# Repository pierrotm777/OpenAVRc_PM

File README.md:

# OpenAVRc_PM
 My own OpenAVRc DEV for test only

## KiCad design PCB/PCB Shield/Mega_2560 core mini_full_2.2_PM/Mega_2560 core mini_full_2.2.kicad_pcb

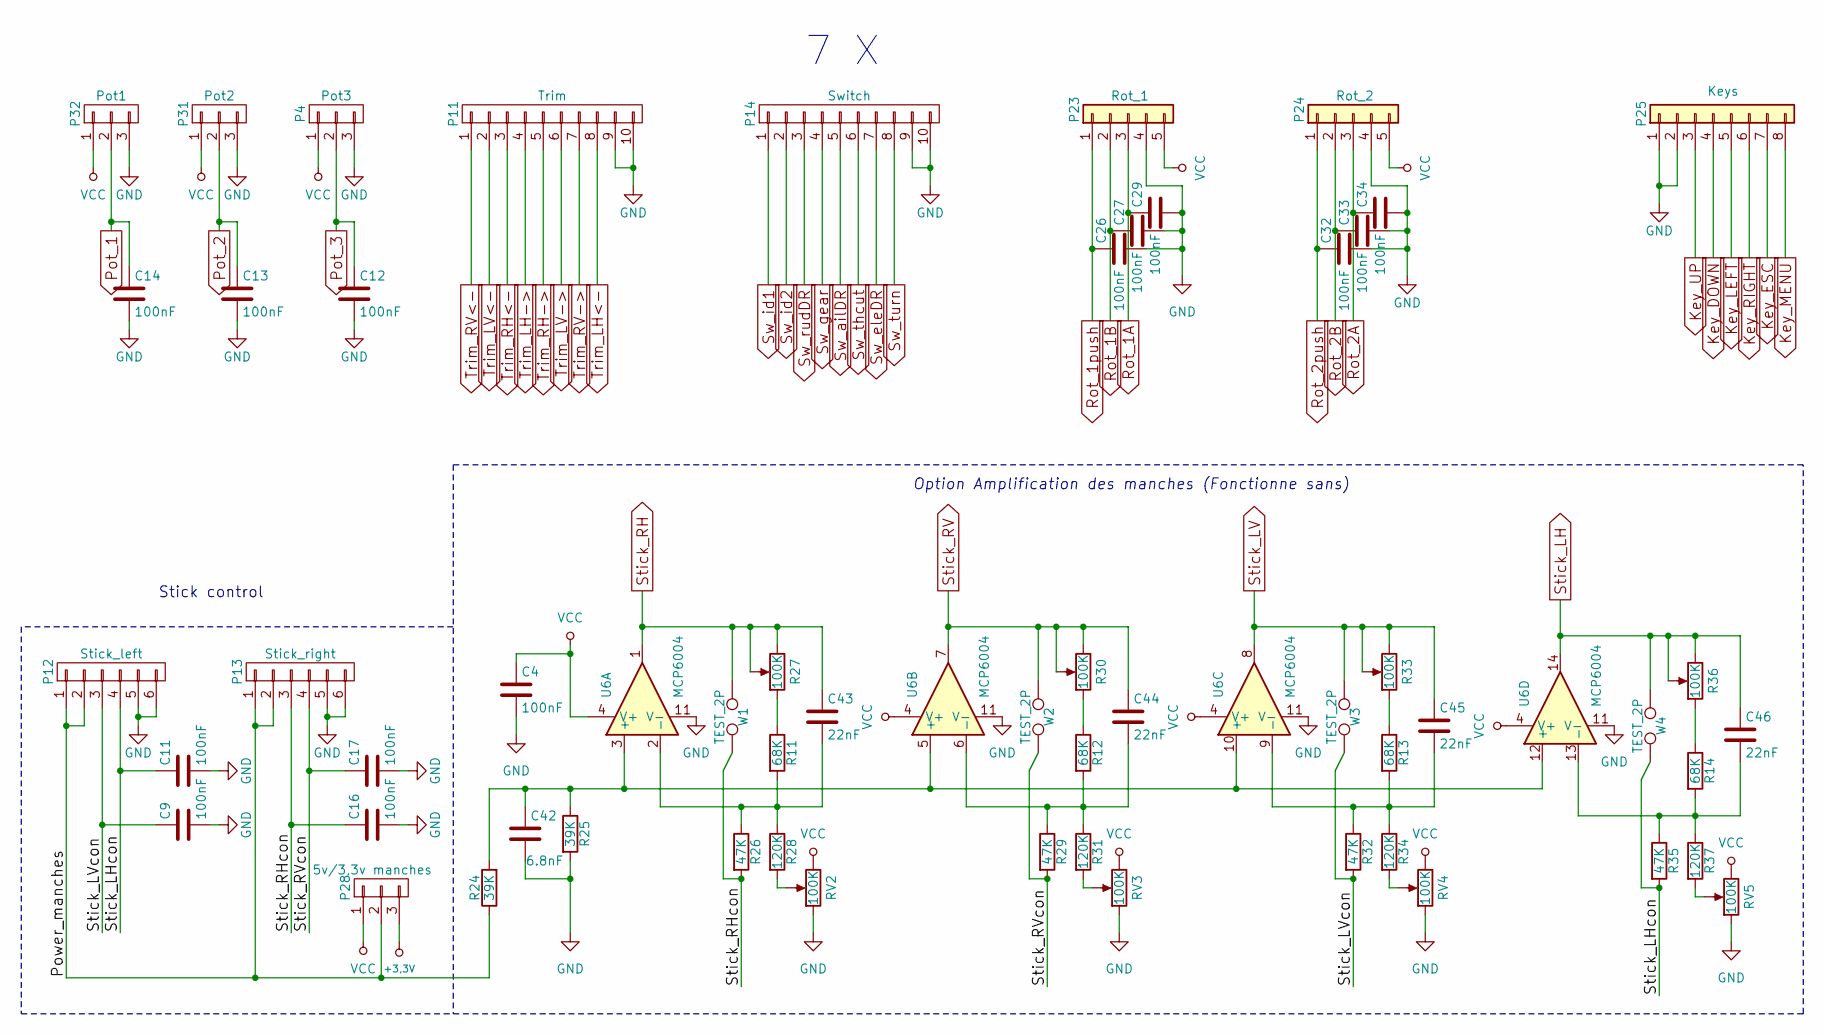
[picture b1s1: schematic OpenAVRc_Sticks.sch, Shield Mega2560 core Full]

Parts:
C4, C9, C11, C12, C13, C14, C16, C17, C26, C27, C29, C32, C33, C34: 100nF; C_1206
C42: 6.8nF; C_1206
C43, C44, C45, C46: 22nF; C_1206
P4: Pot3; Pin_Header_Straight_1x03_Pitch2.54mm
P11: Trim; Pin_Header_Straight_2x05_Pitch2.54mm
P12: Stick_left; Pin_Header_Straight_2x03_Pitch2.54mm
P13: Stick_right; Pin_Header_Straight_2x03_Pitch2.54mm
P14: Switch; Pin_Header_Straight_2x05_Pitch2.54mm
P23: Rot_1; Pin_Header_Straight_1x05_Pitch2.54mm
P24: Rot_2; Pin_Header_Straight_1x05_Pitch2.54mm
P25: Keys; Pin_Header_Straight_2x04_Pitch2.54mm
P28: 5v/3,3v manches; Pin_Header_Straight_1x03_Pitch2.54mm
P31: Pot2; Pin_Header_Straight_1x03_Pitch2.54mm
P32: Pot1; Pin_Header_Straight_1x03_Pitch2.54mm
R11, R12, R13, R14: 68K; R_1206
R24, R25: 39K; R_1206
R26, R29, R32, R35: 47K; R_1206
R27, R30, R33, R36: 100K; Potentiometer_Trimmer_Bourns_3296W
R28, R31, R34, R37: 120K; R_1206
RV2, RV3, RV4, RV5: 100K; Potentiometer_Bourns_3296W_3-8Zoll_Inline_ScrewUp
U6: MCP6004; SOP14
W1, W2, W3, W4: TEST_2P; TESTPT

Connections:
+3.3V: P28.3; also elsewhere on the board
/OpenAVRc_Sticks/Power_manches: P12.1, P12.2, P13.1, P13.2, P28.2, R24.1
/OpenAVRc_Sticks/Stick_LHcon: C11.1, P12.4, R35.2, W4.2
/OpenAVRc_Sticks/Stick_LVcon: C9.1, P12.3, R32.2, W3.2
/OpenAVRc_Sticks/Stick_RHcon: C16.1, P13.3, R26.2, W1.2
/OpenAVRc_Sticks/Stick_RVcon: C17.1, P13.4, R29.2, W2.2
GND: C4.2, C9.2, C11.2, C12.2, C13.2, C14.2, C16.2, C17.2, C26.2, C27.2, C29.2, C32.2, C33.2, C34.2, C42.2, P4.3, P11.9, P11.10, P12.5, P12.6, P13.5, P13.6, P14.9, P14.10, P23.4, P24.4, P25.1, P25.2, P31.3, P32.3, R25.2, RV2.1, RV3.1, RV4.1, RV5.1, U6.11 (V-); also elsewhere on the board
Key_DOWN: P25.4; also elsewhere on the board
Key_ESC: P25.7; also elsewhere on the board
Key_LEFT: P25.5; also elsewhere on the board
Key_MENU: P25.8; also elsewhere on the board
Key_RIGHT: P25.6; also elsewhere on the board
Key_UP: P25.3; also elsewhere on the board
unnamed: C42.1, R24.2, R25.1, U6.3 (+), U6.5 (+), U6.10 (+), U6.12 (+)
unnamed: C43.2, R11.2, R26.1, R28.1, U6.2 (-)
unnamed: C44.2, R12.2, R29.1, R31.1, U6.6 (-)
unnamed: C45.2, R13.2, R32.1, R34.1, U6.9 (-)
unnamed: C46.2, R14.2, R35.1, R37.1, U6.13 (-)
unnamed: R11.1, R27.1
unnamed: R12.1, R30.1
unnamed: R13.1, R33.1
unnamed: R14.1, R36.1
unnamed: R28.2, RV2.2
unnamed: R31.2, RV3.2
unnamed: R34.2, RV4.2
unnamed: R37.2, RV5.2
Pot_1: C14.1, P32.2; also elsewhere on the board
Pot_2: C13.1, P31.2; also elsewhere on the board
Pot_3: C12.1, P4.2; also elsewhere on the board
Rot_1A: C29.1, P23.3; also elsewhere on the board
Rot_1B: C27.1, P23.2; also elsewhere on the board
Rot_1push: C26.1, P23.1; also elsewhere on the board
Rot_2A: C34.1, P24.3; also elsewhere on the board
Rot_2B: C33.1, P24.2; also elsewhere on the board
Rot_2push: C32.1, P24.1; also elsewhere on the board
Stick_LH: C46.1, R36.2, R36.3, U6.14, W4.1; also elsewhere on the board
Stick_LV: C45.1, R33.2, R33.3, U6.8, W3.1; also elsewhere on the board
Stick_RH: C43.1, R27.2, R27.3, U6.1, W1.1; also elsewhere on the board
Stick_RV: C44.1, R30.2, R30.3, U6.7, W2.1; also elsewhere on the board
Sw_ailDR: P14.5; also elsewhere on the board
Sw_eleDR: P14.7; also elsewhere on the board
Sw_gear: P14.4; also elsewhere on the board
Sw_id1: P14.1; also elsewhere on the board
Sw_id2: P14.2; also elsewhere on the board
Sw_rudDR: P14.3; also elsewhere on the board
Sw_thcut: P14.6; also elsewhere on the board
Sw_turn: P14.8; also elsewhere on the board
Trim_LH->: P11.4; also elsewhere on the board
Trim_LH<-: P11.8; also elsewhere on the board
Trim_LV->: P11.6; also elsewhere on the board
Trim_LV<-: P11.2; also elsewhere on the board
Trim_RH->: P11.5; also elsewhere on the board
Trim_RH<-: P11.3; also elsewhere on the board
Trim_RV->: P11.7; also elsewhere on the board
Trim_RV<-: P11.1; also elsewhere on the board
VCC: C4.1, P4.1, P23.5, P24.5, P28.1, P31.1, P32.1, RV2.3, RV3.3, RV4.3, RV5.3, U6.4 (V+); also elsewhere on the board

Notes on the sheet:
Stick control
Option Amplification des manches (Fonctionne sans)
7 X

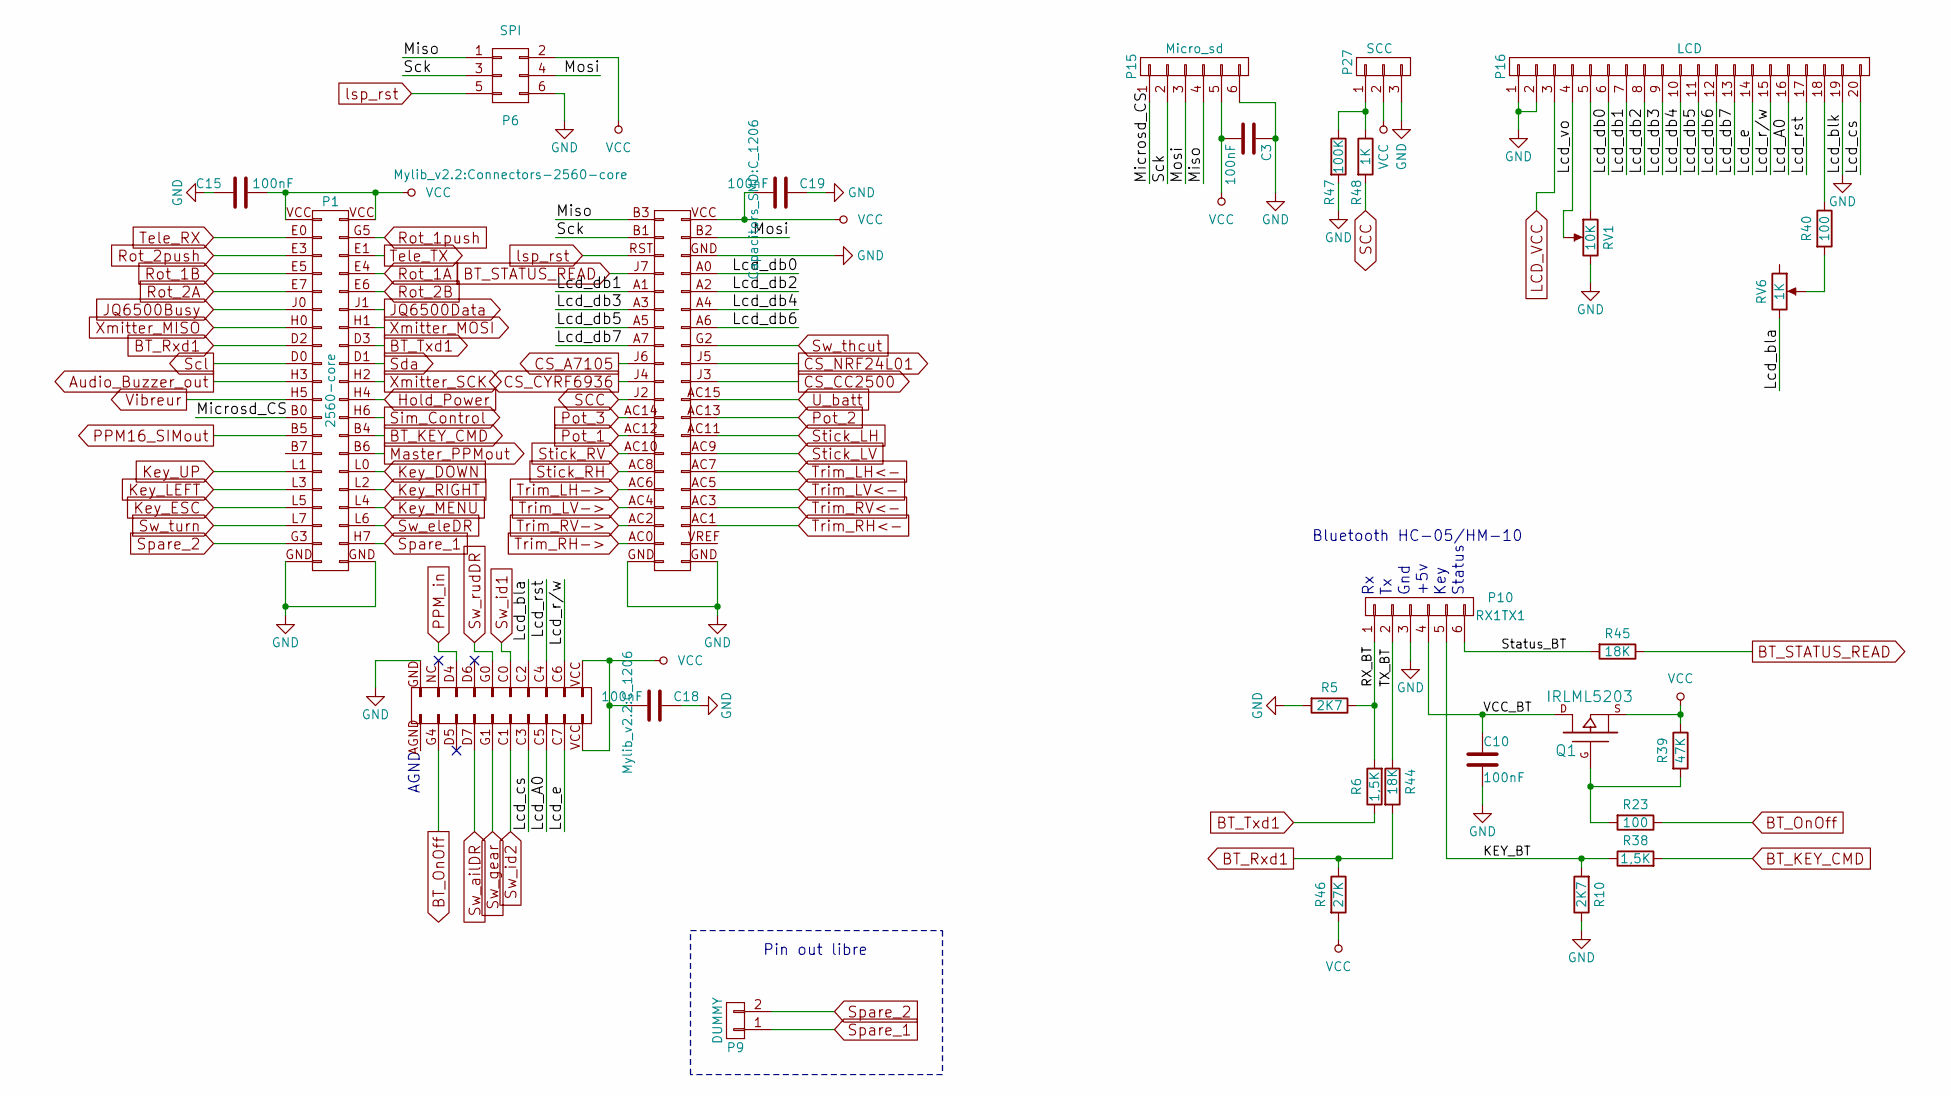
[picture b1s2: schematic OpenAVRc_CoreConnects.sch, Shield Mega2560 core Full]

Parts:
C3, C10, C15, C18, C19: 100nF; C_1206
P1: 2560-core; Connectors-2560-core
P6: SPI; Pin_Header_Straight_2x03_Pitch2.54mm
P9: DUMMY; Pin_Header_Straight_1x02_Pitch2.54mm
P10: RX1TX1; Pin_Header_Straight_1x06_Pitch2.54mm
P15: Micro_sd; Pin_Header_Straight_1x06_Pitch2.54mm
P16: LCD; Pin_Header_Straight_2x10_Pitch2.54mm
P27: SCC; Pin_Header_Straight_1x03_Pitch2.54mm
Q1: IRLML5203; SOT-23_MOS_P
R5, R10: 2K7; R_1206
R6, R38: 1,5K; R_1206
R23, R40: 100; R_1206
R39: 47K; R_1206
R44, R45: 18K; R_1206
R46: 27K; R_1206
R47: 100K; R_1206
R48: 1K; R_1206
RV1: 10K; Potentiometer_Trimmer_Bourns_3296W
RV6: 1K; Potentiometer_Trimmer_Bourns_3296W

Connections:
/OpenAVRc_CoreConnects/KEY_BT: P10.5, R10.2, R38.1
/OpenAVRc_CoreConnects/Lcd_A0: P1.C5 (P85), P16.16
/OpenAVRc_CoreConnects/Lcd_bla: P1.C2 (P88), RV6.3
/OpenAVRc_CoreConnects/Lcd_cs: P1.C3 (P87), P16.20
/OpenAVRc_CoreConnects/Lcd_db0: P1.A0 (P74), P16.6
/OpenAVRc_CoreConnects/Lcd_db1: P1.A1 (P71), P16.7
/OpenAVRc_CoreConnects/Lcd_db2: P1.A2 (P72), P16.8
/OpenAVRc_CoreConnects/Lcd_db3: P1.A3 (P69), P16.9
/OpenAVRc_CoreConnects/Lcd_db4: P1.A4 (P70), P16.10
/OpenAVRc_CoreConnects/Lcd_db5: P1.A5 (P67), P16.11
/OpenAVRc_CoreConnects/Lcd_db6: P1.A6 (P68), P16.12
/OpenAVRc_CoreConnects/Lcd_db7: P1.A7 (P65), P16.13
/OpenAVRc_CoreConnects/Lcd_e: P1.C7 (P83), P16.14
/OpenAVRc_CoreConnects/Lcd_r/w: P1.C6 (P84), P16.15
/OpenAVRc_CoreConnects/Lcd_rst: P1.C4 (P86), P16.17
/OpenAVRc_CoreConnects/Lcd_vo: P16.4, RV1.2
/OpenAVRc_CoreConnects/Microsd_CS: P1.B0 (P24), P15.1
/OpenAVRc_CoreConnects/Miso: P1.B3 (P79), P6.1, P15.4
/OpenAVRc_CoreConnects/Mosi: P1.B2 (P78), P6.4, P15.3
/OpenAVRc_CoreConnects/RX_BT: P10.1, R5.1, R6.2
/OpenAVRc_CoreConnects/Sck: P1.B1 (P77), P6.3, P15.2
/OpenAVRc_CoreConnects/Status_BT: P10.6, R45.2
/OpenAVRc_CoreConnects/TX_BT: P10.2, R44.1
/OpenAVRc_CoreConnects/VCC_BT: C10.1, P10.4, Q1.D
Audio_Buzzer_out: P1.H3 (P20); also elsewhere on the board
BT_KEY_CMD: P1.B4 (P25), R38.2
BT_OnOff: P1.G4 (P97), R23.1
BT_Rxd1: P1.D2 (P16), R44.2, R46.1
BT_STATUS_READ: P1.J7 (P73), R45.1
BT_Txd1: P1.D3 (P15), R6.1
CS_A7105: P1.J6 (P63); also elsewhere on the board
CS_CC2500: P1.J3 (P62); also elsewhere on the board
CS_CYRF6936: P1.J4 (P61); also elsewhere on the board
CS_NRF24L01: P1.J5 (P64); also elsewhere on the board
GND: C3.1, C10.2, C15.1, C18.1, C19.1, P1.GND (P100), P6.6, P10.3, P15.6, P16.1, P16.2, P16.19, P27.3, R5.2, R10.1, R47.2, RV1.3; also elsewhere on the board
Hold_Power: P1.H4 (P21); also elsewhere on the board
JQ6500Busy: P1.J0 (P12); also elsewhere on the board
JQ6500Data: P1.J1 (P11); also elsewhere on the board
Key_DOWN: P1.L0 (P29); also elsewhere on the board
Key_ESC: P1.L5 (P34); also elsewhere on the board
Key_LEFT: P1.L3 (P32); also elsewhere on the board
Key_MENU: P1.L4 (P33); also elsewhere on the board
Key_RIGHT: P1.L2 (P31); also elsewhere on the board
Key_UP: P1.L1 (P30); also elsewhere on the board
LCD_VCC: P16.3; also elsewhere on the board
Master_PPMout: P1.B6 (P27); also elsewhere on the board
unnamed: P16.5, RV1.1
unnamed: P16.18, R40.1
unnamed: P27.1, R47.1, R48.1
unnamed: Q1.G, R23.2, R39.2
unnamed: R40.2, RV6.2
PPM16_SIMout: P1.B5 (P26); also elsewhere on the board
PPM_in: P1.D4 (P96); also elsewhere on the board
Pot_1: P1.AC12 (P55); also elsewhere on the board
Pot_2: P1.AC13 (P58); also elsewhere on the board
Pot_3: P1.AC14 (P57); also elsewhere on the board
Rot_1A: P1.E4 (P7); also elsewhere on the board
Rot_1B: P1.E5 (P8); also elsewhere on the board
Rot_1push: P1.G5 (P3); also elsewhere on the board
Rot_2A: P1.E7 (P10); also elsewhere on the board
Rot_2B: P1.E6 (P9); also elsewhere on the board
Rot_2push: P1.E3 (P6); also elsewhere on the board
SCC: P1.J2 (P59), R48.2
Scl: P1.D0 (P18); also elsewhere on the board
Sda: P1.D1 (P17); also elsewhere on the board
Sim_Control: P1.H6 (P23); also elsewhere on the board
Spare_1: P1.H7 (P37), P9.1
Spare_2: P1.G3 (P38), P9.2
Stick_LH: P1.AC11 (P56); also elsewhere on the board
Stick_LV: P1.AC9 (P54); also elsewhere on the board
Stick_RH: P1.AC8 (P51); also elsewhere on the board
Stick_RV: P1.AC10 (P53); also elsewhere on the board
Sw_ailDR: P1.D7 (P93); also elsewhere on the board
Sw_eleDR: P1.L6 (P35); also elsewhere on the board
Sw_gear: P1.G1 (P91); also elsewhere on the board
Sw_id1: P1.C0 (P90); also elsewhere on the board
Sw_id2: P1.C1 (P89); also elsewhere on the board
Sw_rudDR: P1.G0 (P92); also elsewhere on the board
Sw_thcut: P1.G2 (P66); also elsewhere on the board
Sw_turn: P1.L7 (P36); also elsewhere on the board
Tele_RX: P1.E0 (P4); also elsewhere on the board
Tele_TX: P1.E1 (P5); also elsewhere on the board
Trim_LH->: P1.AC6 (P49); also elsewhere on the board
Trim_LH<-: P1.AC7 (P52); also elsewhere on the board
Trim_LV->: P1.AC4 (P47); also elsewhere on the board
Trim_LV<-: P1.AC5 (P50); also elsewhere on the board
Trim_RH->: P1.AC0 (P43); also elsewhere on the board
Trim_RH<-: P1.AC1 (P46); also elsewhere on the board
Trim_RV->: P1.AC2 (P45); also elsewhere on the board
Trim_RV<-: P1.AC3 (P48); also elsewhere on the board
U_batt: P1.AC15 (P60); also elsewhere on the board
VCC: C3.2, C15.2, C18.2, C19.2, P1.VCC (P1), P6.2, P15.5, P27.2, Q1.S, R39.1, R46.2; also elsewhere on the board
Vibreur: P1.H5 (P22); also elsewhere on the board
Xmitter_MISO: P1.H0 (P14); also elsewhere on the board
Xmitter_MOSI: P1.H1 (P13); also elsewhere on the board
Xmitter_SCK: P1.H2 (P19); also elsewhere on the board
lsp_rst: P1.RST (P75), P6.5; also elsewhere on the board

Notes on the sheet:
Bluetooth HC-05/HM-10
Pin out libre
AGND
Gnd
+5v
Key
Status

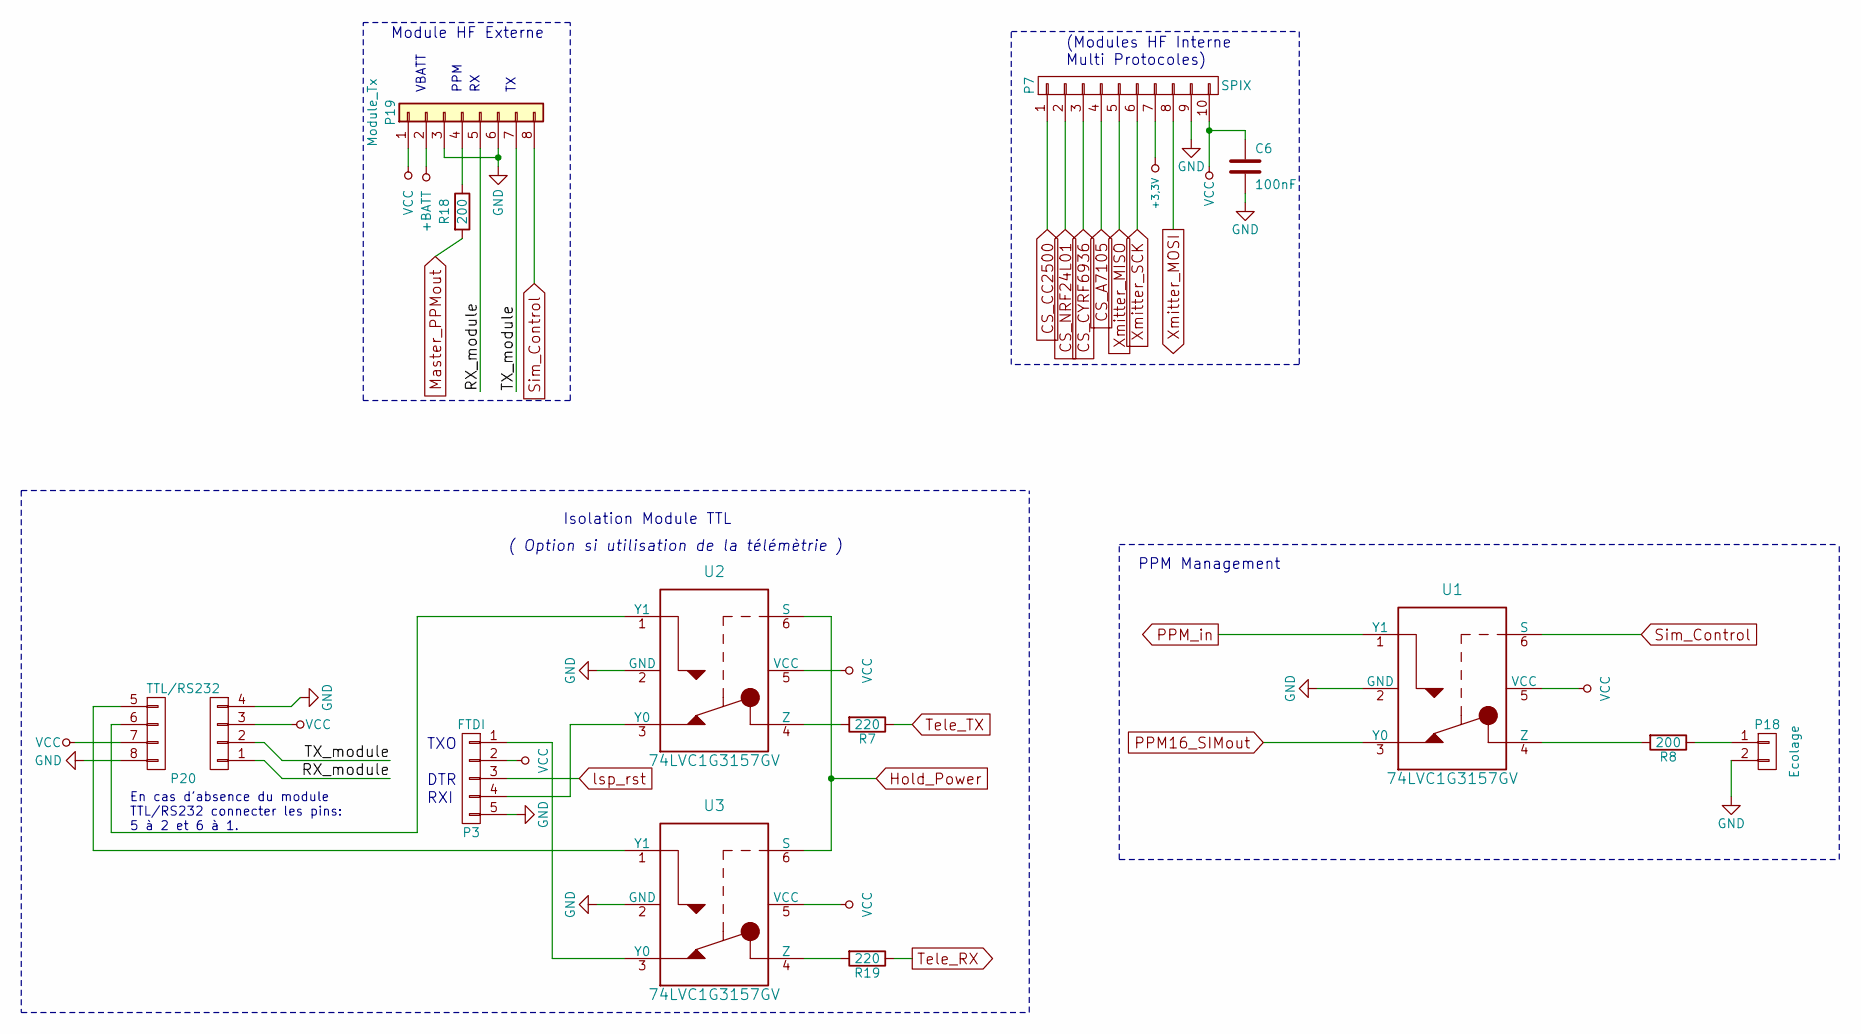
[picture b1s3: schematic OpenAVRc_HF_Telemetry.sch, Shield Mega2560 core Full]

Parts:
C6: 100nF; C_1206
P3: FTDI; Pin_Header_Straight_1x05_Pitch2.54mm
P7: SPIX; Pin_Header_Straight_2x05_Pitch2.54mm
P18: Ecolage; Pin_Header_Straight_1x02_Pitch2.54mm
P19: Module_Tx; Pin_Header_Straight_2x04_Pitch2.54mm
P20: TTL/RS232; Con_RS232_TTL
R7, R19: 220; R_1206
R8, R18: 200; R_1206
U1, U2, U3: 74LVC1G3157GV; SOT-457

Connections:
+3.3V: P7.7; also elsewhere on the board
+BATT: P19.2; also elsewhere on the board
/OpenAVRc_HF_Telemetry/RX_module: P19.5, P20.1
/OpenAVRc_HF_Telemetry/TX_module: P19.7, P20.2
CS_A7105: P7.4; also elsewhere on the board
CS_CC2500: P7.1; also elsewhere on the board
CS_CYRF6936: P7.3; also elsewhere on the board
CS_NRF24L01: P7.2; also elsewhere on the board
GND: C6.2, P3.5, P7.9, P18.2, P19.3, P19.6, P20.4, P20.8, U1.2 (GND), U2.2 (GND), U3.2 (GND); also elsewhere on the board
Hold_Power: U2.6 (S), U3.6 (S); also elsewhere on the board
Master_PPMout: R18.2; also elsewhere on the board
unnamed: P3.1, U3.3 (Y0)
unnamed: P3.4, U2.3 (Y0)
unnamed: P18.1, R8.1
unnamed: P19.4, R18.1
unnamed: P20.5, U3.1 (Y1)
unnamed: P20.6, U2.1 (Y1)
unnamed: R7.2, U2.4 (Z)
unnamed: R8.2, U1.4 (Z)
unnamed: R19.2, U3.4 (Z)
PPM16_SIMout: U1.3 (Y0); also elsewhere on the board
PPM_in: U1.1 (Y1); also elsewhere on the board
Sim_Control: P19.8, U1.6 (S); also elsewhere on the board
Tele_RX: R19.1; also elsewhere on the board
Tele_TX: R7.1; also elsewhere on the board
VCC: C6.1, P3.2, P7.10, P19.1, P20.3, P20.7, U1.5 (VCC), U2.5 (VCC), U3.5 (VCC); also elsewhere on the board
Xmitter_MISO: P7.5; also elsewhere on the board
Xmitter_MOSI: P7.8; also elsewhere on the board
Xmitter_SCK: P7.6; also elsewhere on the board
lsp_rst: P3.3; also elsewhere on the board

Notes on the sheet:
Isolation Module TTL
PPM Management
( Option si utilisation de la télémètrie )
Module HF Externe
(Modules HF Interne Multi Protocoles)
TXO
RXI
DTR
PPM
VBATT
En cas d'absence du module TTL/RS232 connecter les pins: 5 à 2 et 6 à 1.

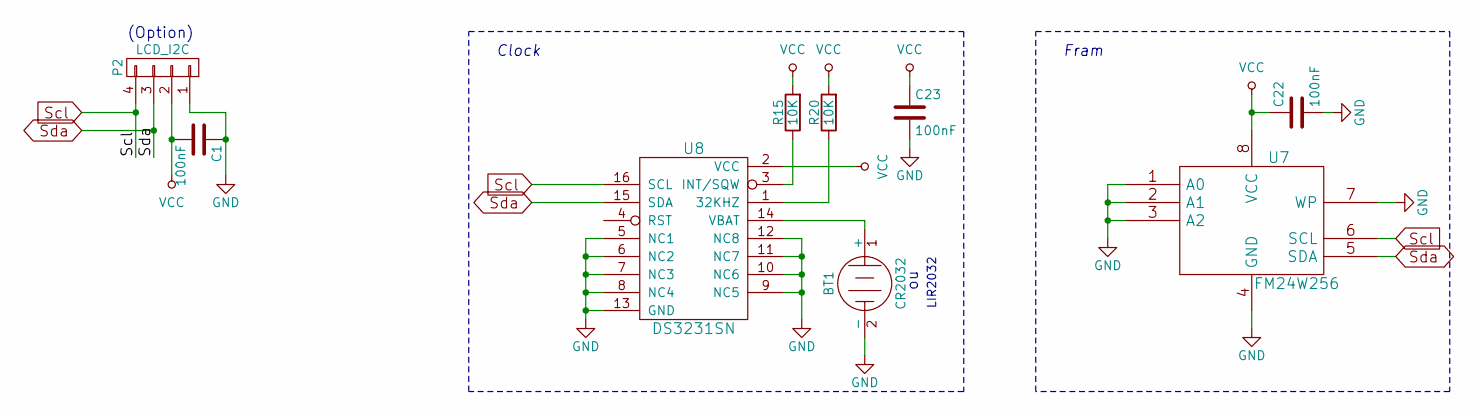
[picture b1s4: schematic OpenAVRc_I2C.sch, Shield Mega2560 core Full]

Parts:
BT1: CR2032; Pin_Header_Straight_1x02_Pitch2.54mm
C1, C22, C23: 100nF; C_1206
P2: LCD_I2C; Pin_Header_Straight_1x04_Pitch2.54mm
R15, R20: 10K; R_1206
U7: FM24W256; SOIC-8-FRAM_DI
U8: DS3231SN; SO-16-DS3231

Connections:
GND: BT1.2 (-), C1.1, C22.2, C23.2, P2.1, U7.1 (A0), U7.2 (A1), U7.3 (A2), U7.4 (GND), U7.7 (WP), U8.5 (NC1), U8.6 (NC2), U8.7 (NC3), U8.8 (NC4), U8.9 (NC5), U8.10 (NC6), U8.11 (NC7), U8.12 (NC8), U8.13 (GND); also elsewhere on the board
unnamed: BT1.1 (+), U8.14 (VBAT)
unnamed: R15.1, U8.3 (INT/SQW)
unnamed: R20.1, U8.1 (32KHZ)
Scl: P2.4, U7.6 (SCL), U8.16 (SCL); also elsewhere on the board
Sda: P2.3, U7.5 (SDA), U8.15 (SDA); also elsewhere on the board
VCC: C1.2, C22.1, C23.1, P2.2, R15.2, R20.2, U7.8 (VCC), U8.2 (VCC); also elsewhere on the board

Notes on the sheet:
Clock
Fram
LIR2032
(Option)

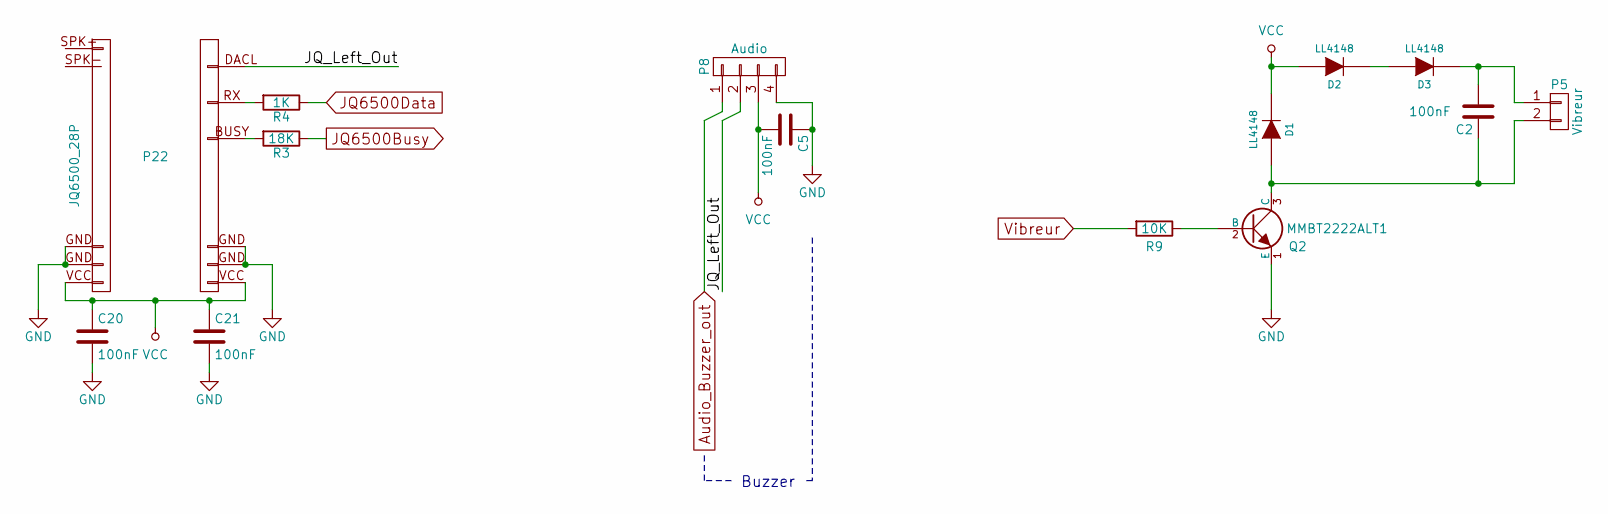
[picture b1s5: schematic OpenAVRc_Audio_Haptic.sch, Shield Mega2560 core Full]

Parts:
C2, C5, C20, C21: 100nF; C_1206
D1, D2, D3: LL4148; D_SOD-123
P5: Vibreur; Pin_Header_Straight_1x02_Pitch2.54mm
P8: Audio; Pin_Header_Straight_1x04_Pitch2.54mm
P22: JQ6500_28P; connector_mini-JQ6500-28P
Q2: MMBT2222ALT1; SOT-23_MMBT2222
R3: 18K; R_1206
R4: 1K; R_1206
R9: 10K; R_1206

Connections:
/OpenAVRc_Audio_Haptic/JQ_Left_Out: P8.2, P22.DACL (P16)
Audio_Buzzer_out: P8.1; also elsewhere on the board
GND: C5.1, C20.2, C21.2, P8.4, P22.GND (P12), Q2.1 (E); also elsewhere on the board
JQ6500Busy: R3.1; also elsewhere on the board
JQ6500Data: R4.1; also elsewhere on the board
unnamed: C2.1, D1.2 (A), P5.2, Q2.3 (C)
unnamed: C2.2, D3.1 (K), P5.1
unnamed: D2.1 (K), D3.2 (A)
unnamed: P22.BUSY (P20), R3.2
unnamed: P22.RX (P18), R4.2
unnamed: Q2.2 (B), R9.1
VCC: C5.2, C20.1, C21.1, D1.1 (K), D2.2 (A), P8.3, P22.VCC (P14); also elsewhere on the board
Vibreur: R9.2; also elsewhere on the board

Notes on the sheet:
Buzzer

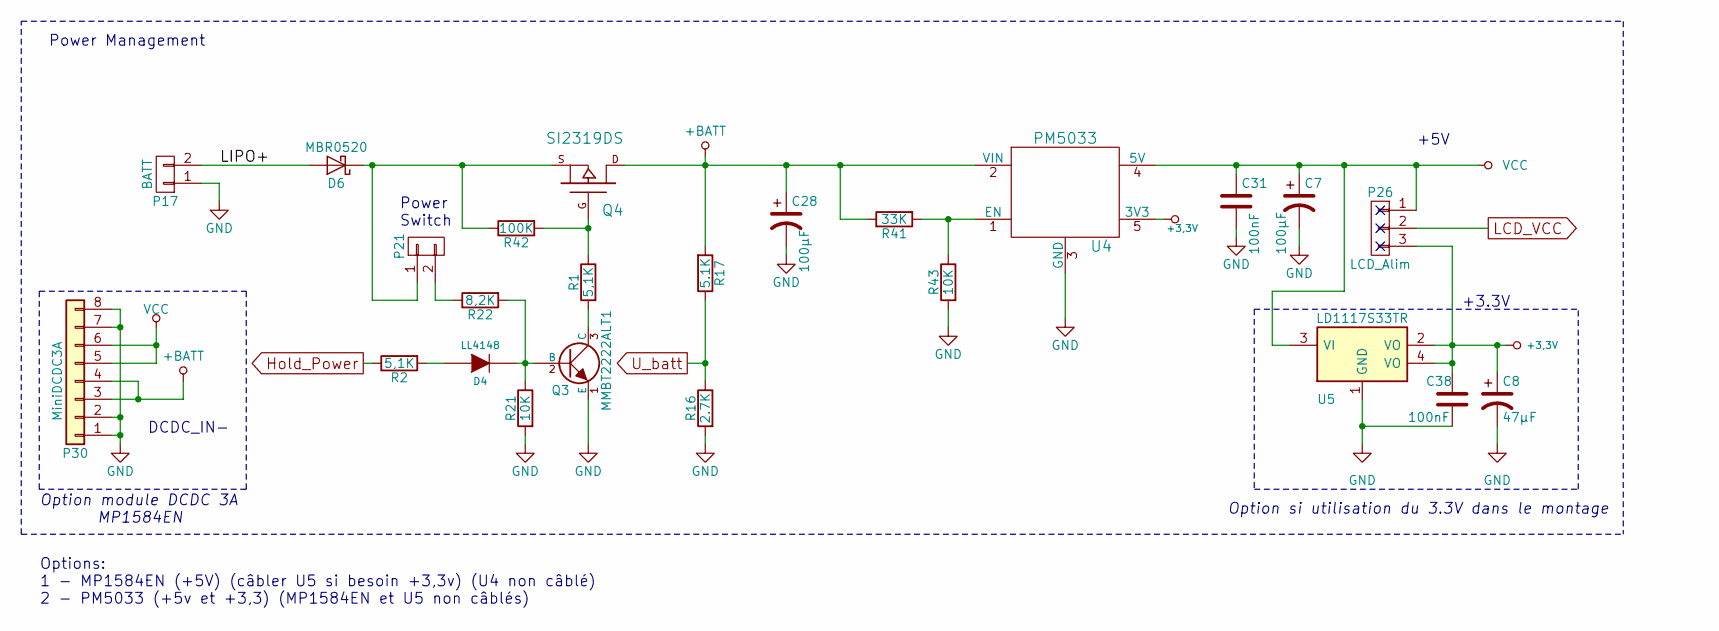
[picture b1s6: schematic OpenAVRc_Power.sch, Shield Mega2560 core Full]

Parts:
C7, C28: 100µF; CP_Elec_6.3x5.3
C8: 47µF; CP_Elec_6.3x5.3
C31, C38: 100nF; C_1206
D4: LL4148; D_SOD-123
D6: MBR0520; D_SOD-123
P17: BATT; Pin_Header_Straight_1x02_Pitch2.54mm
P21: Sw_power; Pin_Header_Straight_1x02_Pitch2.54mm
P26: LCD_Alim; Pin_Header_Straight_1x03_Pitch2.54mm
P30: MiniDCDC3A
Q3: MMBT2222ALT1; SOT-23_MMBT2222
Q4: SI2319DS; SOT-23_MOS_P
R1, R2: 5,1K; R_1206
R16: 2.7K; R_1206
R17: 5.1K; R_1206
R21, R43: 10K; R_1206
R22: 8,2K; R_1206
R41: 33K; R_1206
R42: 100K; R_1206
U4: PM5033; Pm5033_sil5
U5: LD1117S33TR; SOT-223

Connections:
+3.3V: C8.1, C38.1, P26.3, U4.5 (3V3), U5.2 (VO), U5.4 (VO); also elsewhere on the board
+BATT: C28.1, P30.3, P30.4, Q4.D, R17.2, R41.1, U4.2 (VIN); also elsewhere on the board
/OpenAVRc_Power/LIPO+: D6.2 (A), P17.2
GND: C7.2, C8.2, C28.2, C31.2, C38.2, P17.1, P30.1, P30.2, P30.7, P30.8, Q3.1 (E), R16.2, R21.2, R43.2, U4.3 (GND), U5.1 (GND); also elsewhere on the board
Hold_Power: R2.1; also elsewhere on the board
LCD_VCC: P26.2; also elsewhere on the board
unnamed: D4.1 (K), Q3.2 (B), R21.1, R22.2
unnamed: D4.2 (A), R2.2
unnamed: D6.1 (K), P21.1, Q4.S, R42.1
unnamed: P21.2, R22.1
unnamed: Q3.3 (C), R1.2
unnamed: Q4.G, R1.1, R42.2
unnamed: R41.2, R43.1, U4.1 (EN)
U_batt: R16.1, R17.1; also elsewhere on the board
VCC: C7.1, C31.1, P26.1, P30.5, P30.6, U4.4 (5V), U5.3 (VI); also elsewhere on the board

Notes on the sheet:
+3.3V
+5V
Power Management
Option si utilisation du 3.3V dans le montage
Power Switch
DCDC_IN-
Option module DCDC 3A MP1584EN
Options: 1 - MP1584EN (+5V) (câbler U5 si besoin +3,3v) (U4 non câblé) 2 - PM5033 (+5v et +3,3) (MP1584EN et U5 non câblés)

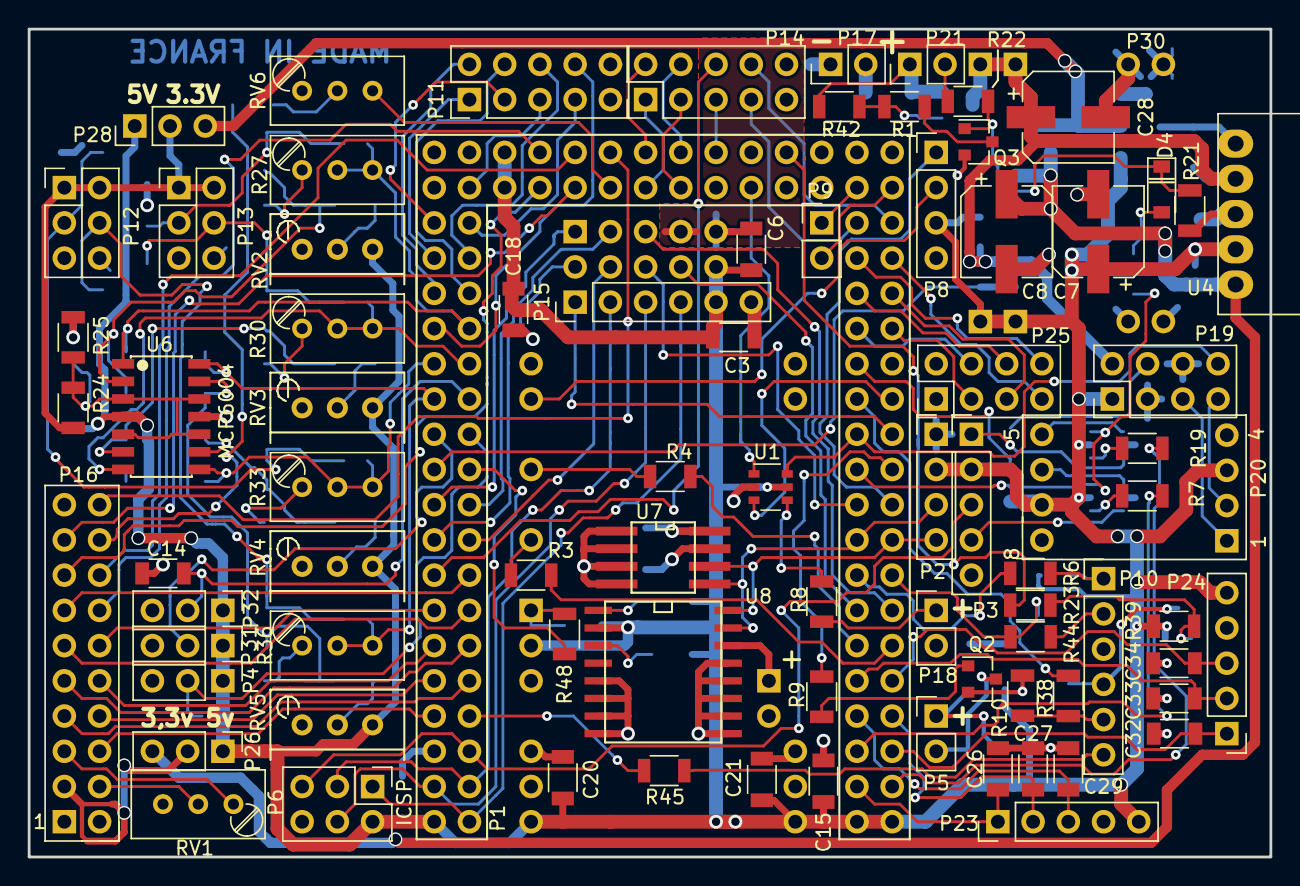
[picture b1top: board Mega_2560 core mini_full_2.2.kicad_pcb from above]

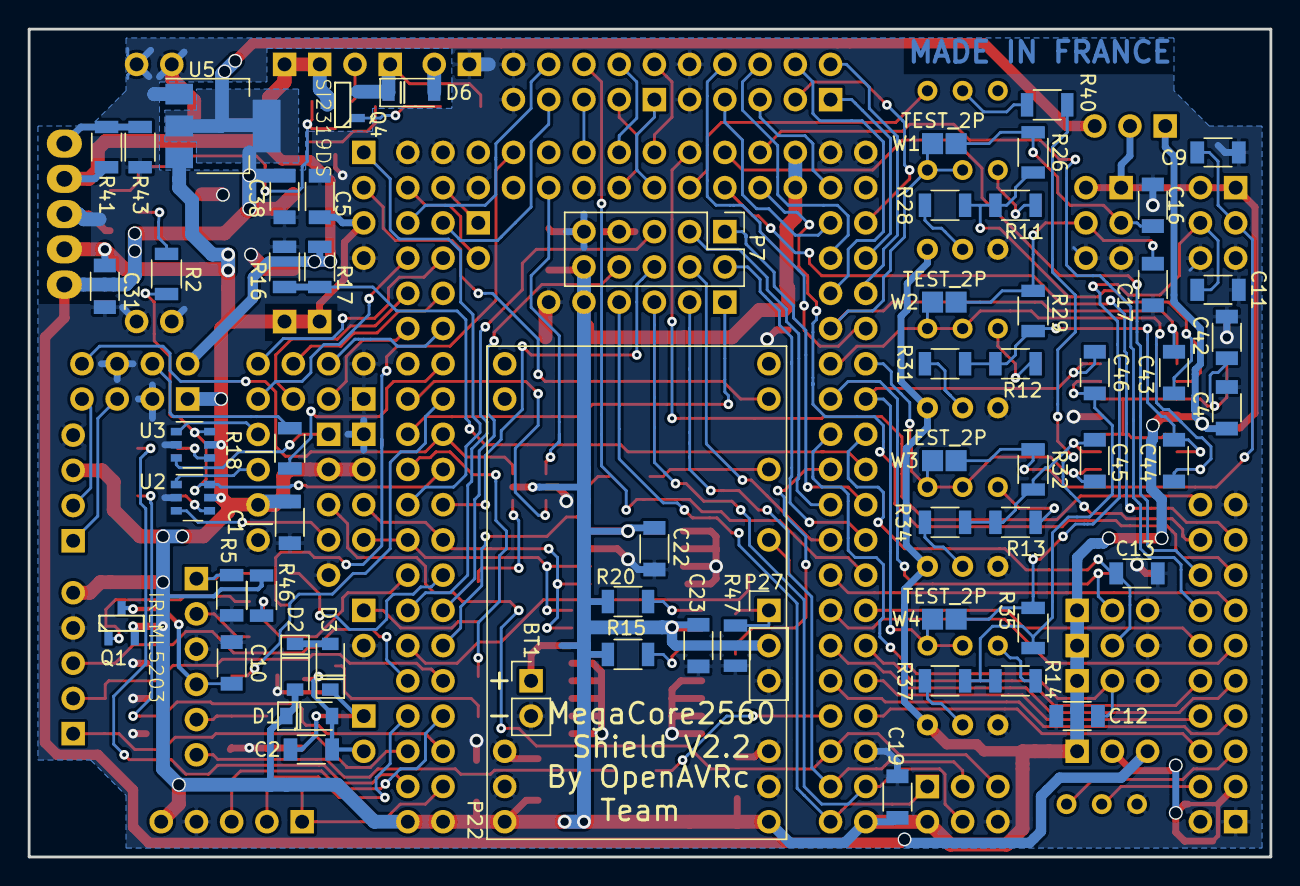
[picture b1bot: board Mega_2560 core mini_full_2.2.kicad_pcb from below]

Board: 2 copper layers, 89.5 x 59.7 mm, 144 parts (62 on the bottom side), 146 nets.

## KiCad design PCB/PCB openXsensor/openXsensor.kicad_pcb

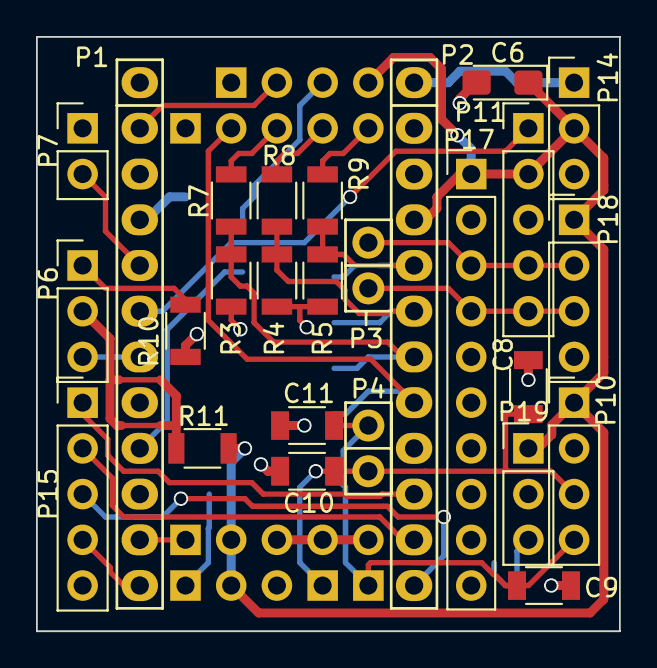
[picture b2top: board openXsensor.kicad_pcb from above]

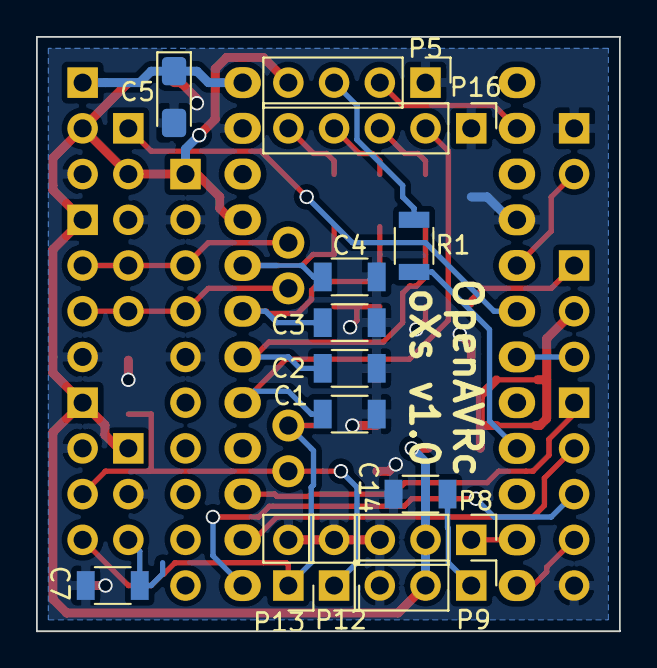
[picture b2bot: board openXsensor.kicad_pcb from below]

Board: 2 copper layers, 32.4 x 33.0 mm, 40 parts (14 on the bottom side), 29 nets.

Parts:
C1, C2, C3, C4, C7, C8, C9, C10, C11, C14: 100nF; C_1206
C5, C6: 10uF; CP_EIA-3216-18_Kemet-A_Pad1.58x1.35mm_HandSolder
P1: Digital; Socket_Strip_Arduino_1x12
P2: Analog; Socket_Strip_Arduino_1x12
P3, P4: ADC; Socket_Strip_Arduino_1x02
P5: GPS; Pin_Header_Straight_1x04_Pitch2.54mm
P6: HUB/SPORT; Pin_Header_Straight_1x03_Pitch2.54mm
P7: PPM; Pin_Header_Straight_1x02_Pitch2.54mm
P8: FUEL; Pin_Header_Straight_1x03_Pitch2.54mm
P9: RPM; Pin_Header_Straight_1x03_Pitch2.54mm
P10: VFAS/COURANT; Pin_Header_Straight_1x04_Pitch2.54mm
P11: GY-86; Pin_Header_Straight_1x05_Pitch2.54mm
P12: NTC1; Pin_Header_Straight_1x02_Pitch2.54mm
P13: NTC2; Pin_Header_Straight_1x02_Pitch2.54mm
P14: ALIM; Pin_Header_Straight_1x03_Pitch2.54mm
P15: SEQUENCEUR; Pin_Header_Straight_1x05_Pitch2.54mm
P16: 4S; Pin_Header_Straight_1x05_Pitch2.54mm
P17: ADS1115; Pin_Header_Straight_1x10_Pitch2.54mm
P18: MS4525DO; Pin_Header_Straight_1x04_Pitch2.54mm
P19: MPXV7002DP; Pin_Header_Straight_1x03_Pitch2.54mm
R1, R3, R5: 10K; R_1206
R4: 12K; R_1206
R7: 8,2K; R_1206
R8: 22K; R_1206
R9: 27K; R_1206
R10: 220; R_1206
R11: 0; R_1206

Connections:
/0(Rx): P1.2, P5.2
/2: P1.5, P7.2
/3(**): P1.6, P11.1
/4: P1.7, P6.3
/6(**): P1.9, R1.1
/8: P1.11, P9.1
/A0: C1.1, P2.8, P16.2
/A1: C2.1, P2.7, R3.1, R7.2
/A2: C3.1, P2.6, R4.1, R8.2
/A3: C4.1, P2.5, R5.1, R9.2
/A4: P3.2, P11.5, P17.4, P18.3
/A5: P3.1, P11.4, P17.3, P18.2
/A6: C8.1, C10.1, P4.2, P10.3, P12.1
/A7: C9.1, C11.1, P4.1, P10.4, P13.1
/RAW: C5.1, P2.1, P14.1
/SEQ1: P1.12, P15.4
/SEQ2: P2.12, P15.3
/SEQ3: P2.11, P15.2
/SEQ4: P2.10, P15.1
GND: C1.2, C2.2, C3.2, C4.2, C5.2, C6.2, C7.2, C8.2, C9.2, C10.2, C11.2, C14.2, P1.4, P2.2, P5.1, P7.1, P8.3, P9.3, P10.2, P11.3, P12.2, P13.2, P14.3, P15.5, P16.1, P17.2, P17.5, P18.4, P19.2, R3.2, R4.2, R5.2, R10.2
unnamed: C7.1, P19.3
unnamed: C14.1, P8.1
unnamed: P5.3, R1.2
unnamed: P6.1, R10.1
unnamed: P6.2, R11.1
unnamed: P16.3, R7.1
unnamed: P16.4, R8.1
unnamed: P16.5, R9.1
VCC: C6.1, P2.4, P5.4, P8.2, P9.2, P10.1, P11.2, P14.2, P17.1, P18.1, P19.1, R11.2

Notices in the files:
OpenAVRc/gui/view_main.cpp:
OpenAVRc is free software: you can redistribute it and/or modify
it under the terms of the GNU General Public License as published by
the Free Software Foundation, either version 2 of the License, or
(at your option) any later version.
License GPLv2: http://www.gnu.org/licenses/gpl-2.0.html
PCB/PCB Shield/Mega_2560 core mini_full_2.2_PM/OpenAVRc_Audio_Haptic.sch:
© Team OpenAVRc
